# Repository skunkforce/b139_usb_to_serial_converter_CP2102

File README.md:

# edgy_board number b139
This design is part of the [edgy board project](https://github.com/skunkforce/edgy_boards). 

# getting started
This repository uses submodules. After cloning use the command 

```$ git submodule update --init --recursive```

to pull the submodules before opening the project with kicad. 

# Tests
Tests can be found in [TESTS.md](TESTS.md)

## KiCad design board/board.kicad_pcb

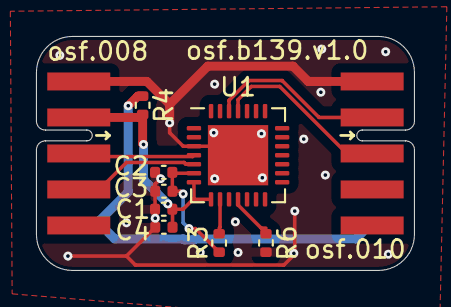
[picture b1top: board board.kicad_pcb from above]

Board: 2 copper layers, 21.0 x 13.0 mm, 11 parts (1 on the bottom side), 10 nets.

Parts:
C1, C2: 100nF; C_0402_1005Metric
C3, C4: 1uF; C_0402_1005Metric
J1: 010_UART; on_edge_2x05_host
J2: 008_USB; on_edge_2x05_device
LOGO1: Logo_Open_Hardware_Small; OSHW-Symbol_6.7x6mm_SilkScreen
R3: 4.7k; R_0402_1005Metric
R4: 0R; R_0402_1005Metric
R6: 10k; R_0402_1005Metric
U1: CP2102N-Axx-xQFN28; QFN-28-1EP_5x5mm_P0.5mm_EP3.35x3.35mm

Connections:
+5V: J1.10 (5V), J2.10 (5V), R4.1
/cp2102/UART_RX: J1.3 (RX), U1.25 (RXD)
/cp2102/USB_DM: J2.4 (DM), U1.5 (D-)
/cp2102/USB_DP: J2.3 (DP), U1.4 (D+)
/cp2102/USB_VBUS: C1.1, C4.1, J2.2 (VBUS), R4.2, U1.7 (VREGIN), U1.8 (VBUS)
/cp2102/USRT_TX: J1.2 (TX), U1.26 (TXD)
/cp2102/~reset: R3.2, U1.9 (~RST)
GND: C1.2, C2.2, C3.2, C4.2, J1.1 (GND), J2.1 (GND), R6.2, U1.3 (GND), U1.29 (GND)
unnamed: C2.1, C3.1, R3.1, U1.6 (VDD)
unnamed: R6.1, U1.11 (~SUSPEND)

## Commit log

2023-06-23 schemetic finished
2023-06-23 finished layout
2024-02-01 added lcsc numbers
2024-02-01 updated image
